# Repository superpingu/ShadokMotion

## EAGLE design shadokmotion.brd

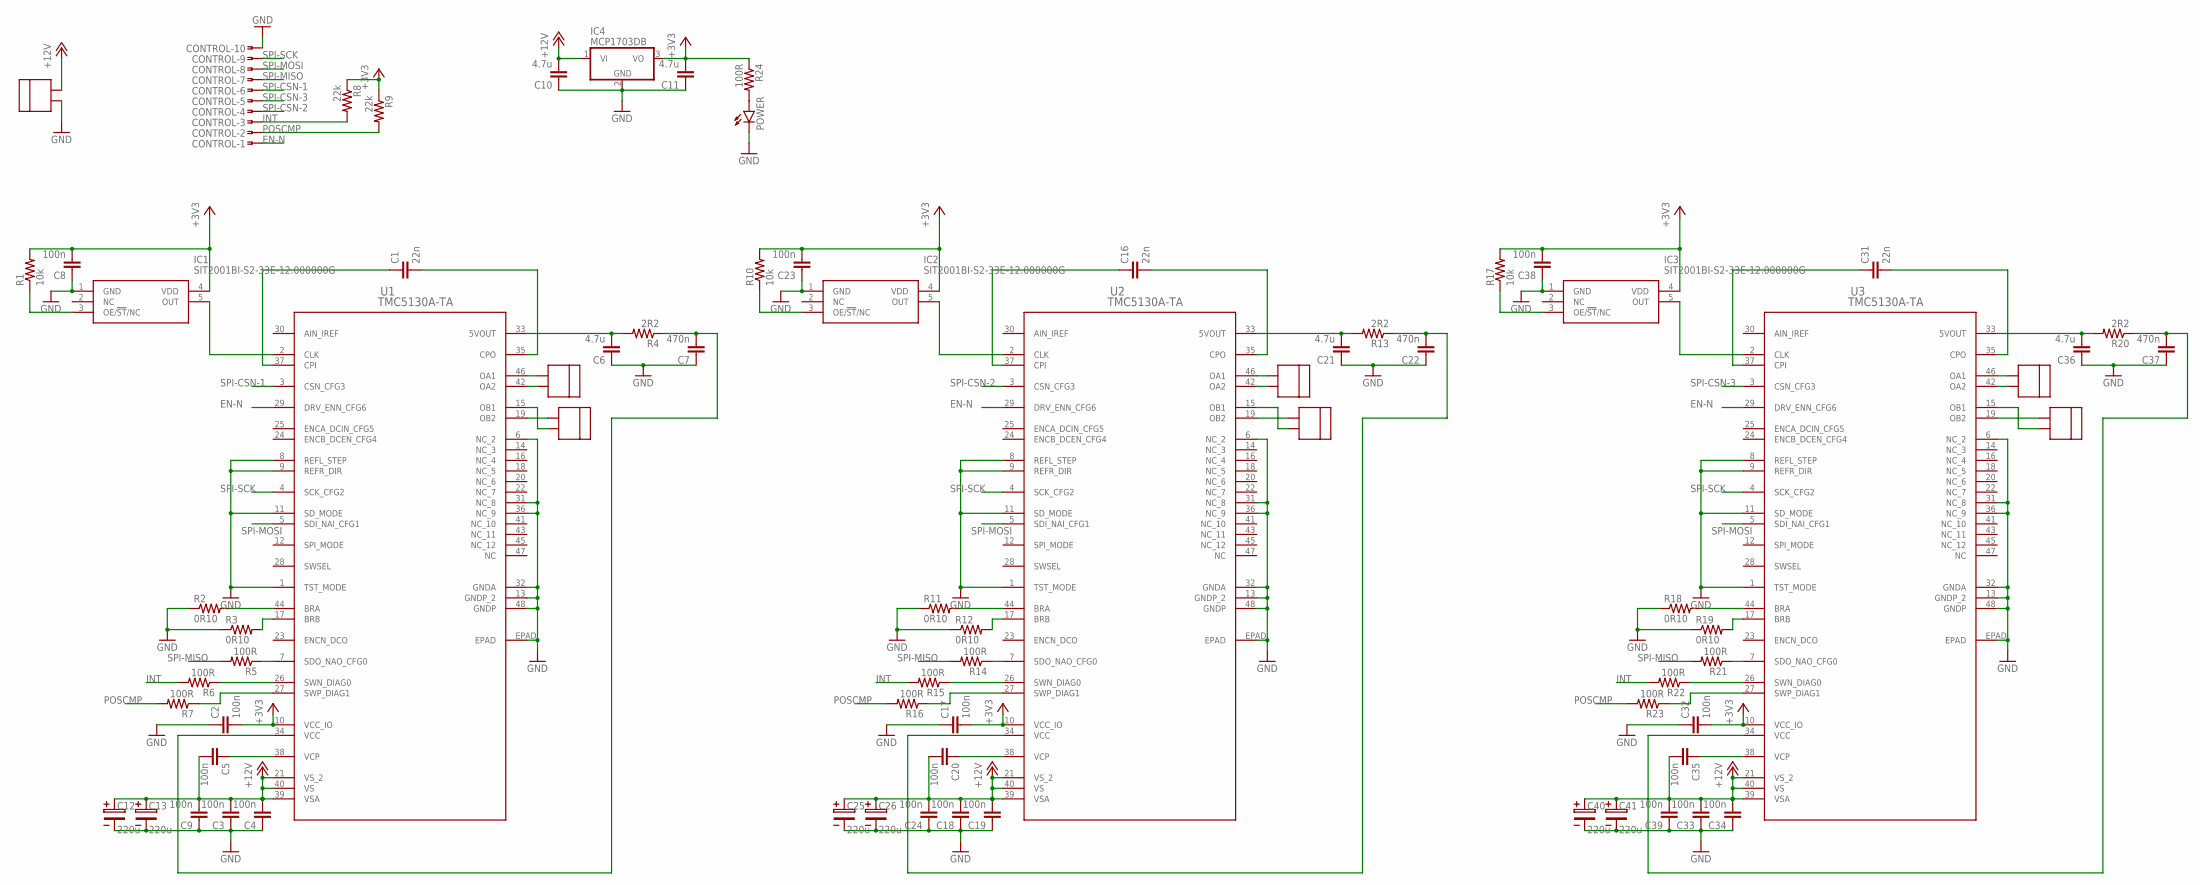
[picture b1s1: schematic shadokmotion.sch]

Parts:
C1, C16, C31: 22n; C0805
C2, C3, C4, C5, C8, C9, C17, C18, C19, C20, C23, C24, C32, C33, C34, C35, C38, C39: 100n; C0805
C6, C10, C11, C21, C36: 4.7u; C0805
C7, C22, C37: 470n; C0805
C12, C13, C25, C26, C40, C41: 220u; 4.4X1.9X4.3(BXCXA)
CONTROL: SMDTOP-10; SMDTOP10
IC1, IC2, IC3: SIT2001BI-S2-33E-12.000000G; SOT95P280X130-5N
IC4: MCP1703DB; SOT223
M1-A, M1-A1, M1-A2, M1-B, M1-B1, M1-B2: CTB5202/2
POWER: LEDCHIPLED_0805; CHIPLED_0805
R1, R10, R17: 10k; R0805
R2, R3, R11, R12, R18, R19: 0R10; R1206
R4, R13, R20: 2R2; R0805
R5, R6, R7, R14, R15, R16, R21, R22, R23, R24: 100R; R0805
R8, R9: 22k; R0805
U1, U2, U3: TMC5130A-TA; ETQFP48_9X9
U$3: CTB5202/2

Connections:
+3V3: C2.2, C8.2, C11.2, C17.2, C23.2, C32.2, C38.2, IC1.4 (VDD), IC2.4 (VDD), IC3.4 (VDD), IC4.3 (VO), R1.2, R8.1, R9.1, R10.2, R17.2, R24.1, U1.10 (VCC_IO), U2.10 (VCC_IO), U3.10 (VCC_IO)
+12V: C3.2, C4.2, C5.2, C9.2, C10.2, C12.1, C13.1, C18.2, C19.2, C20.2, C24.2, C25.1, C26.1, C33.2, C34.2, C35.2, C39.2, C40.1, C41.1, IC4.1 (VI), U1.21 (VS_2), U1.39 (VSA), U1.40 (VS), U2.21 (VS_2), U2.39 (VSA), U2.40 (VS), U3.21 (VS_2), U3.39 (VSA), U3.40 (VS), U$3.P$2 (2)
EN-N: CONTROL.1, U1.29 (DRV_ENN_CFG6), U2.29 (DRV_ENN_CFG6), U3.29 (DRV_ENN_CFG6)
GND: C2.1, C3.1, C4.1, C6.1, C7.1, C8.1, C9.1, C10.1, C11.1, C12.2, C13.2, C17.1, C18.1, C19.1, C21.1, C22.1, C23.1, C24.1, C25.2, C26.2, C32.1, C33.1, C34.1, C36.1, C37.1, C38.1, C39.1, C40.2, C41.2, CONTROL.10, IC1.1 (GND), IC2.1 (GND), IC3.1 (GND), IC4.2 (GND), POWER.C, R2.1, R3.1, R11.1, R12.1, R18.1, R19.1, U1.1 (TST_MODE), U1.6 (NC_2), U1.8 (REFL_STEP), U1.9 (REFR_DIR), U1.11 (SD_MODE), U1.13 (GNDP_2), U1.31 (NC_8), U1.32 (GNDA), U1.36 (NC_9), U1.48 (GNDP), U1.EPAD, U2.1 (TST_MODE), U2.6 (NC_2), U2.8 (REFL_STEP), U2.9 (REFR_DIR), U2.11 (SD_MODE), U2.13 (GNDP_2), U2.31 (NC_8), U2.32 (GNDA), U2.36 (NC_9), U2.48 (GNDP), U2.EPAD, U3.1 (TST_MODE), U3.6 (NC_2), U3.8 (REFL_STEP), U3.9 (REFR_DIR), U3.11 (SD_MODE), U3.13 (GNDP_2), U3.31 (NC_8), U3.32 (GNDA), U3.36 (NC_9), U3.48 (GNDP), U3.EPAD, U$3.P$1 (1)
INT: CONTROL.3, R6.2, R8.2, R15.2, R22.2
unnamed: C1.1, U1.37 (CPI)
unnamed: C1.2, U1.35 (CPO)
unnamed: IC1.5 (OUT), U1.2 (CLK)
unnamed: IC1.3 (OE/!ST!/NC), R1.1
unnamed: M1-A.P$1 (1), U1.46 (OA1)
unnamed: M1-A.P$2 (2), U1.42 (OA2)
unnamed: M1-B.P$1 (1), U1.19 (OB2)
unnamed: M1-B.P$2 (2), U1.15 (OB1)
unnamed: C5.1, U1.38 (VCP)
unnamed: R2.2, U1.44 (BRA)
unnamed: R3.2, U1.17 (BRB)
unnamed: C6.2, R4.2, U1.33 (5VOUT)
unnamed: R7.1, U1.27 (SWP_DIAG1)
unnamed: C7.2, R4.1, U1.34 (VCC)
unnamed: R6.1, U1.26 (SWN_DIAG0)
unnamed: R5.1, U1.7 (SDO_NAO_CFG0)
unnamed: C16.1, U2.37 (CPI)
unnamed: C16.2, U2.35 (CPO)
unnamed: IC2.5 (OUT), U2.2 (CLK)
unnamed: IC2.3 (OE/!ST!/NC), R10.1
unnamed: M1-A1.P$1 (1), U2.46 (OA1)
unnamed: M1-A1.P$2 (2), U2.42 (OA2)
unnamed: M1-B1.P$1 (1), U2.19 (OB2)
unnamed: M1-B1.P$2 (2), U2.15 (OB1)
unnamed: C20.1, U2.38 (VCP)
unnamed: R11.2, U2.44 (BRA)
unnamed: R12.2, U2.17 (BRB)
unnamed: C21.2, R13.2, U2.33 (5VOUT)
unnamed: C22.2, R13.1, U2.34 (VCC)
unnamed: R15.1, U2.26 (SWN_DIAG0)
unnamed: R14.1, U2.7 (SDO_NAO_CFG0)
unnamed: R16.1, U2.27 (SWP_DIAG1)
unnamed: C31.1, U3.37 (CPI)
unnamed: C31.2, U3.35 (CPO)
unnamed: IC3.5 (OUT), U3.2 (CLK)
unnamed: IC3.3 (OE/!ST!/NC), R17.1
unnamed: M1-A2.P$1 (1), U3.46 (OA1)
unnamed: M1-A2.P$2 (2), U3.42 (OA2)
unnamed: M1-B2.P$1 (1), U3.19 (OB2)
unnamed: M1-B2.P$2 (2), U3.15 (OB1)
unnamed: C35.1, U3.38 (VCP)
unnamed: R18.2, U3.44 (BRA)
unnamed: R19.2, U3.17 (BRB)
unnamed: C36.2, R20.2, U3.33 (5VOUT)
unnamed: C37.2, R20.1, U3.34 (VCC)
unnamed: R22.1, U3.26 (SWN_DIAG0)
unnamed: R21.1, U3.7 (SDO_NAO_CFG0)
unnamed: R23.1, U3.27 (SWP_DIAG1)
unnamed: POWER.A, R24.2
POSCMP: CONTROL.2, R7.2, R9.2, R16.2, R23.2
SPI-CSN-1: CONTROL.6, U1.3 (CSN_CFG3)
SPI-CSN-2: CONTROL.4, U2.3 (CSN_CFG3)
SPI-CSN-3: CONTROL.5, U3.3 (CSN_CFG3)
SPI-MISO: CONTROL.7, R5.2, R14.2, R21.2
SPI-MOSI: CONTROL.8, U1.5 (SDI_NAI_CFG1), U2.5 (SDI_NAI_CFG1), U3.5 (SDI_NAI_CFG1)
SPI-SCK: CONTROL.9, U1.4 (SCK_CFG2), U2.4 (SCK_CFG2), U3.4 (SCK_CFG2)

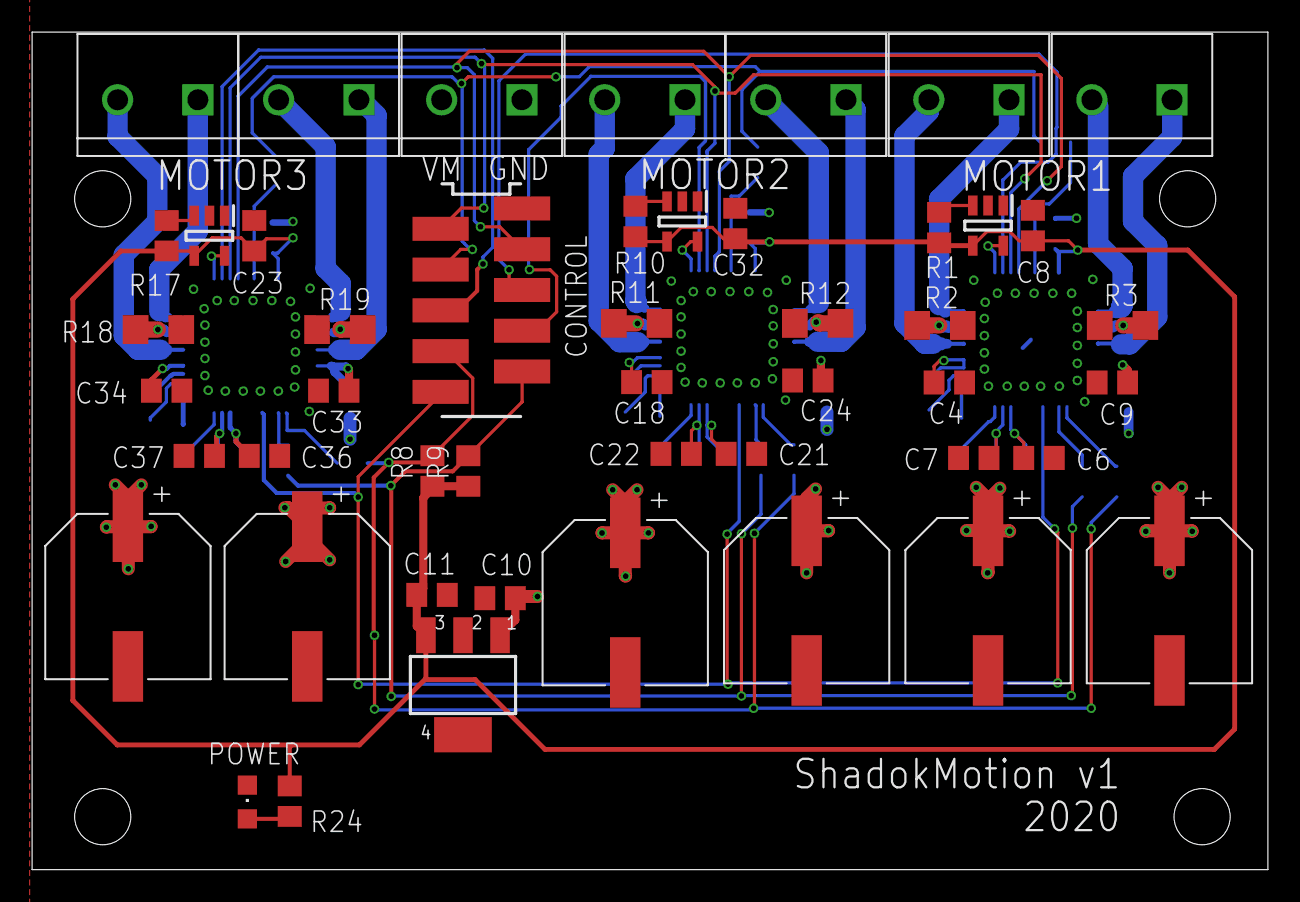
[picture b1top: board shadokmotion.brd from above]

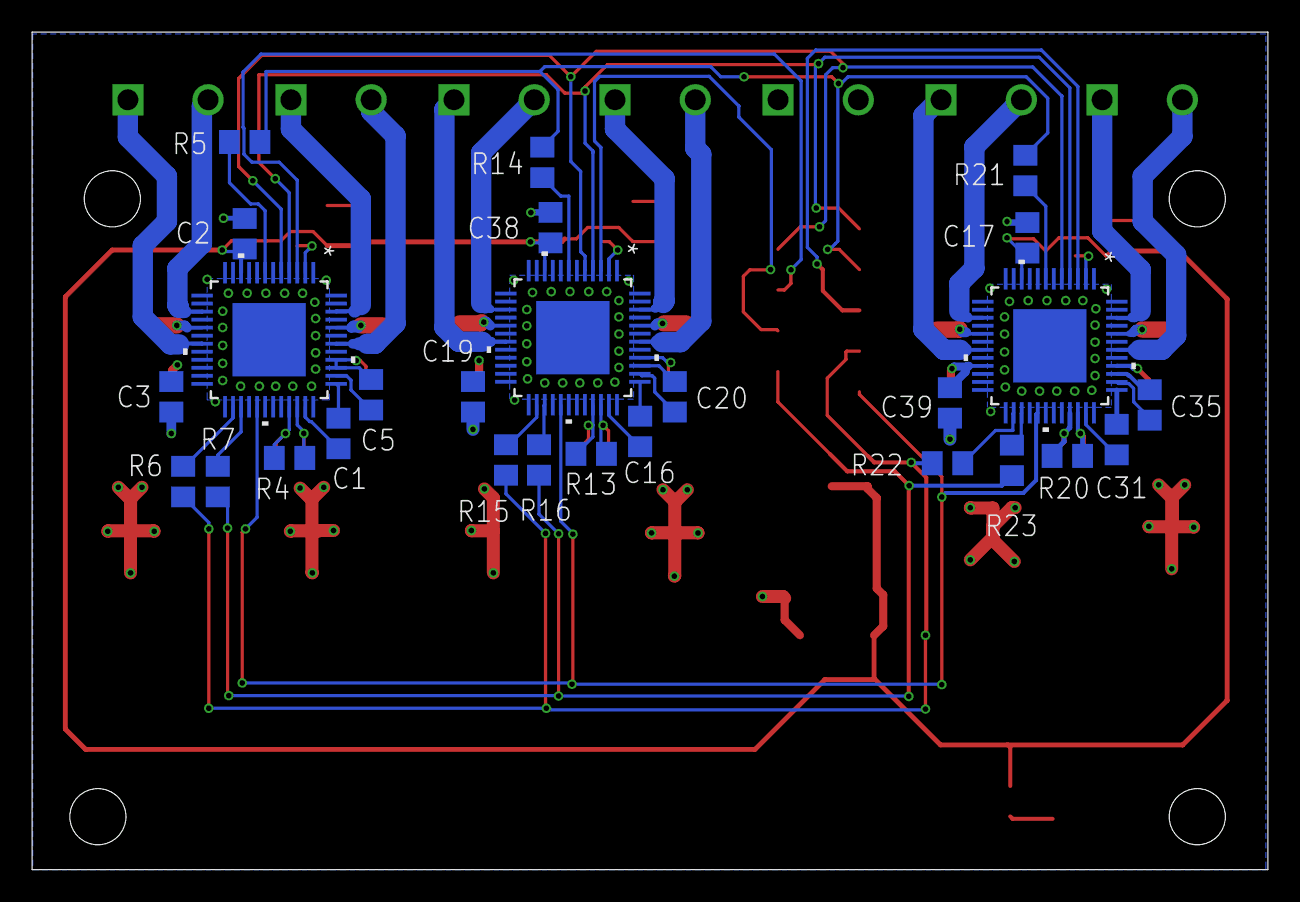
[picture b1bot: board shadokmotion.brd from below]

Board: 2 copper layers, 77.0 x 52.2 mm, 75 parts (27 on the bottom side), 61 nets.

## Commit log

2020-03-07 added BOM

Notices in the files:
parts and their libraries:
Wurth_Elektronik_Passive_Capacitors_rev1: Copyright: Würth Elektronik
COPYRIGHT: Copyright (C) 2016 Accelerated Designs. All rights reserved
